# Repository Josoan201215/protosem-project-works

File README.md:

# Protosem Project Works

## Overview

This repository documents my engineering projects and practical work associated with Protosem. It serves as a centralized record of electronics prototyping, hardware development, PCB design, mechanical CAD, robotics, and intelligent manufacturing systems.

The objective is to develop practical engineering solutions through iterative design, prototyping, testing, and documentation.

## Development Approach

Each project should include its objective, requirements, design files, implementation details, test results, limitations, and future improvements.

Designs and results will be updated as development progresses. Proposed features will be distinguished from implemented and verified features.

## Tools and Technologies

* KiCad — electronic schematic and PCB design
* Fusion 360 — mechanical CAD and product design
* Python — scripting and AI development
* ROS 2 — robotics software and simulation

## Author

Engineering project portfolio maintained as part of Protosem project development.

## Note

This repository is a work in progress. Project descriptions represent the current development scope; implementation and test status will be updated as evidence becomes available.

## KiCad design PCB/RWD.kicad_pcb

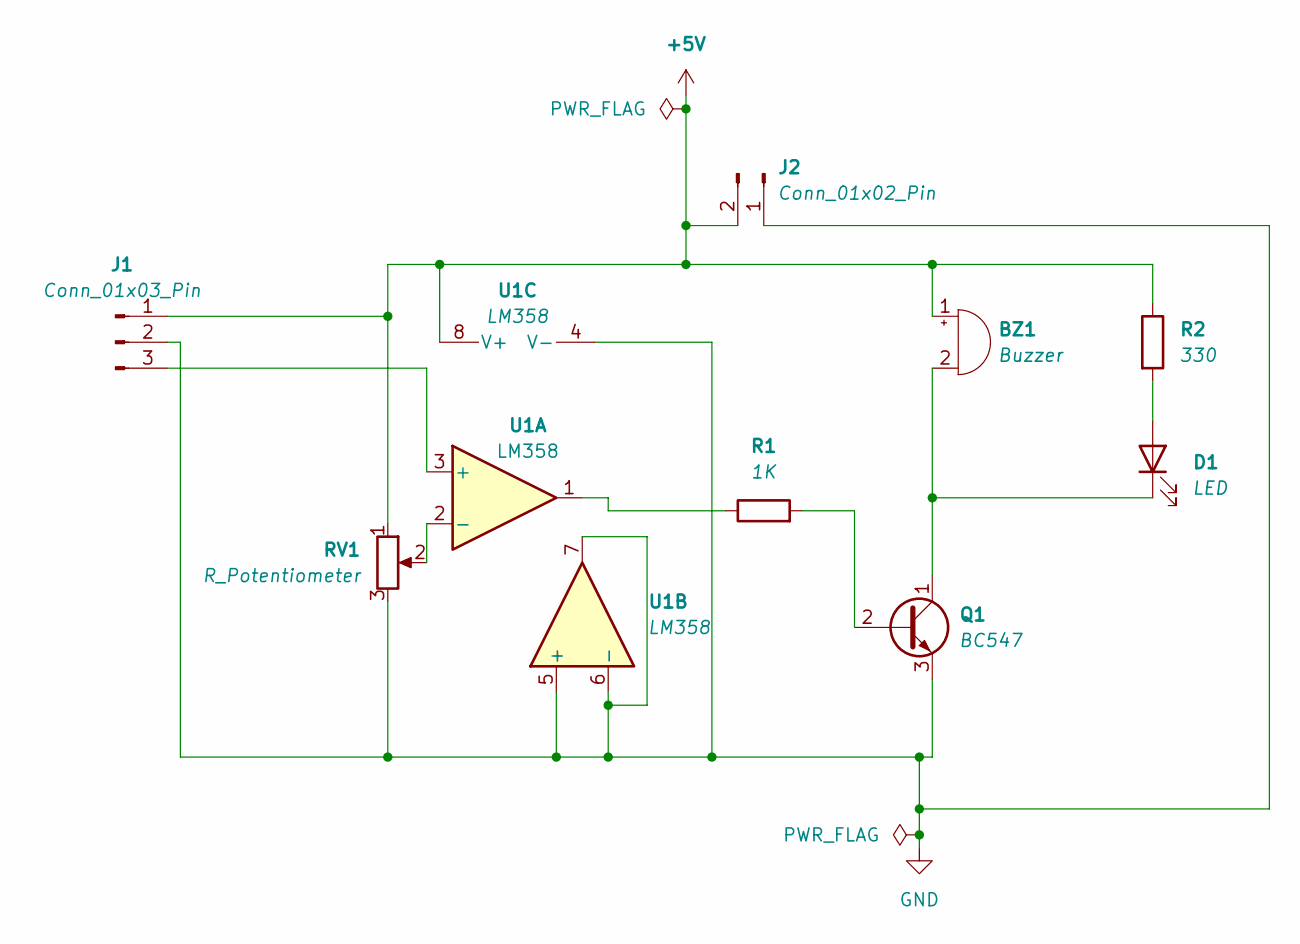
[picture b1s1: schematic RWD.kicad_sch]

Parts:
BZ1: Buzzer; Buzzer_12x9.5RM7.6
D1: LED; LED_D5.0mm
J1: Conn_01x03_Pin; PinHeader_1x03_P2.54mm_Vertical
J2: Conn_01x02_Pin; PinHeader_1x02_P2.54mm_Vertical
Q1: BC547; TO-92_Inline
R1: 1K; R_Axial_DIN0207_L6.3mm_D2.5mm_P10.16mm_Horizontal
R2: 330; R_Axial_DIN0207_L6.3mm_D2.5mm_P10.16mm_Horizontal
RV1: R_Potentiometer; Potentiometer_Bourns_3296Y_Vertical
U1: LM358; DIP-8_W7.62mm

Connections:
+5V: BZ1.1 (+), J1.1, J2.2, R2.1, RV1.1, U1.8 (V+)
GND: J1.2, J2.1, Q1.3 (E), RV1.3, U1.4 (V-), U1.5 (+), U1.6 (-), U1.7
unnamed: BZ1.2 (-), D1.1 (K), Q1.1 (C)
unnamed: D1.2 (A), R2.2
unnamed: J1.3, U1.3 (+)
unnamed: Q1.2 (B), R1.2
unnamed: R1.1, U1.1
unnamed: RV1.2, U1.2 (-)

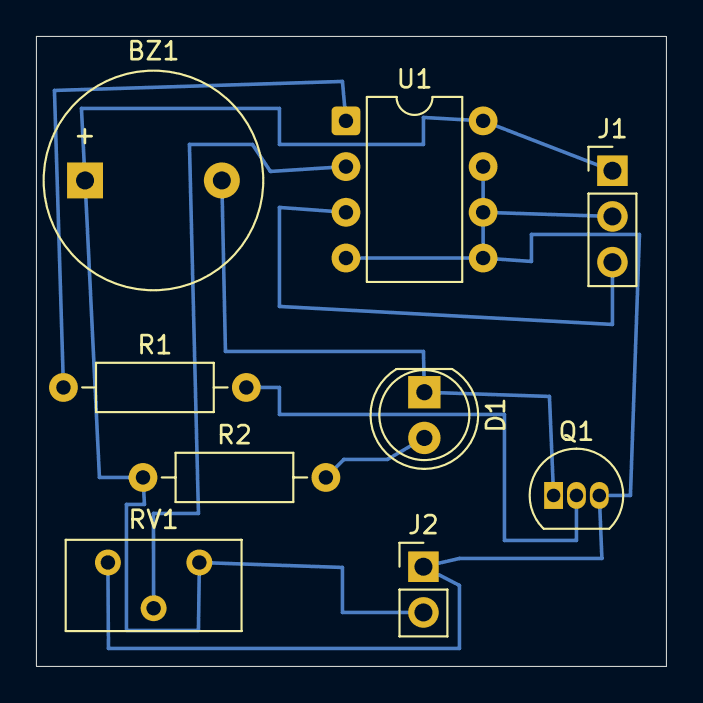
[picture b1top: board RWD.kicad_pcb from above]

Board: 2 copper layers, 35.0 x 35.0 mm, 9 parts (0 on the bottom side), 8 nets.

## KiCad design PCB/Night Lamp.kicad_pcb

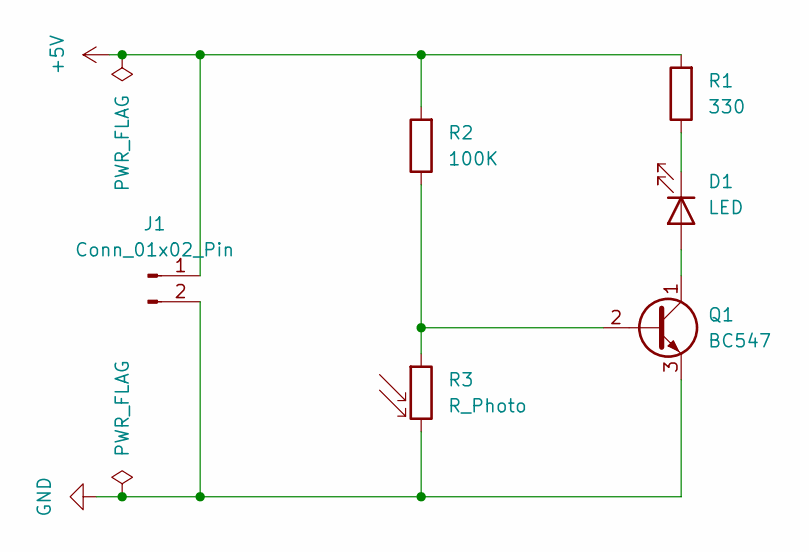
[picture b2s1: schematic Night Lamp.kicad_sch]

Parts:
D1: LED; LED_D5.0mm
J1: Conn_01x02_Pin; PinHeader_1x02_P2.54mm_Vertical
Q1: BC547; TO-92_Inline
R1: 330; R_Axial_DIN0207_L6.3mm_D2.5mm_P10.16mm_Horizontal
R2: 100K; R_Axial_DIN0207_L6.3mm_D2.5mm_P10.16mm_Horizontal
R3: R_Photo; R_LDR_5.1x4.3mm_P3.4mm_Vertical

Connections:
+5V: J1.1, R1.2, R2.2
GND: J1.2, Q1.3 (E), R3.2
unnamed: D1.2 (A), Q1.1 (C)
unnamed: D1.1 (K), R1.1
unnamed: Q1.2 (B), R2.1, R3.1

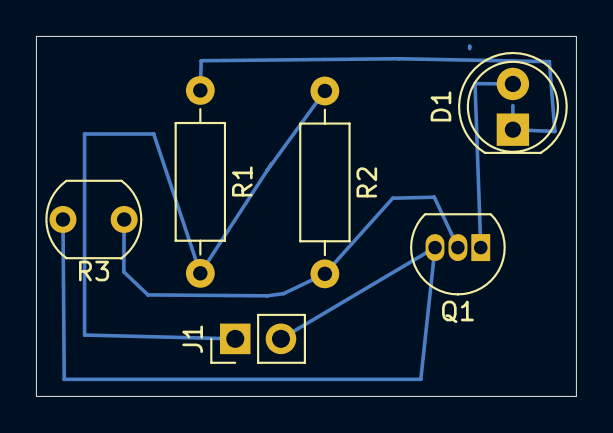
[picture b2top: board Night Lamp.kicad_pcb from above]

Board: 2 copper layers, 30.0 x 20.0 mm, 6 parts (0 on the bottom side), 5 nets.
